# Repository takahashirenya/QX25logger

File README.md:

# QX25logger
25年度鳥人間コンテストのロガー基盤

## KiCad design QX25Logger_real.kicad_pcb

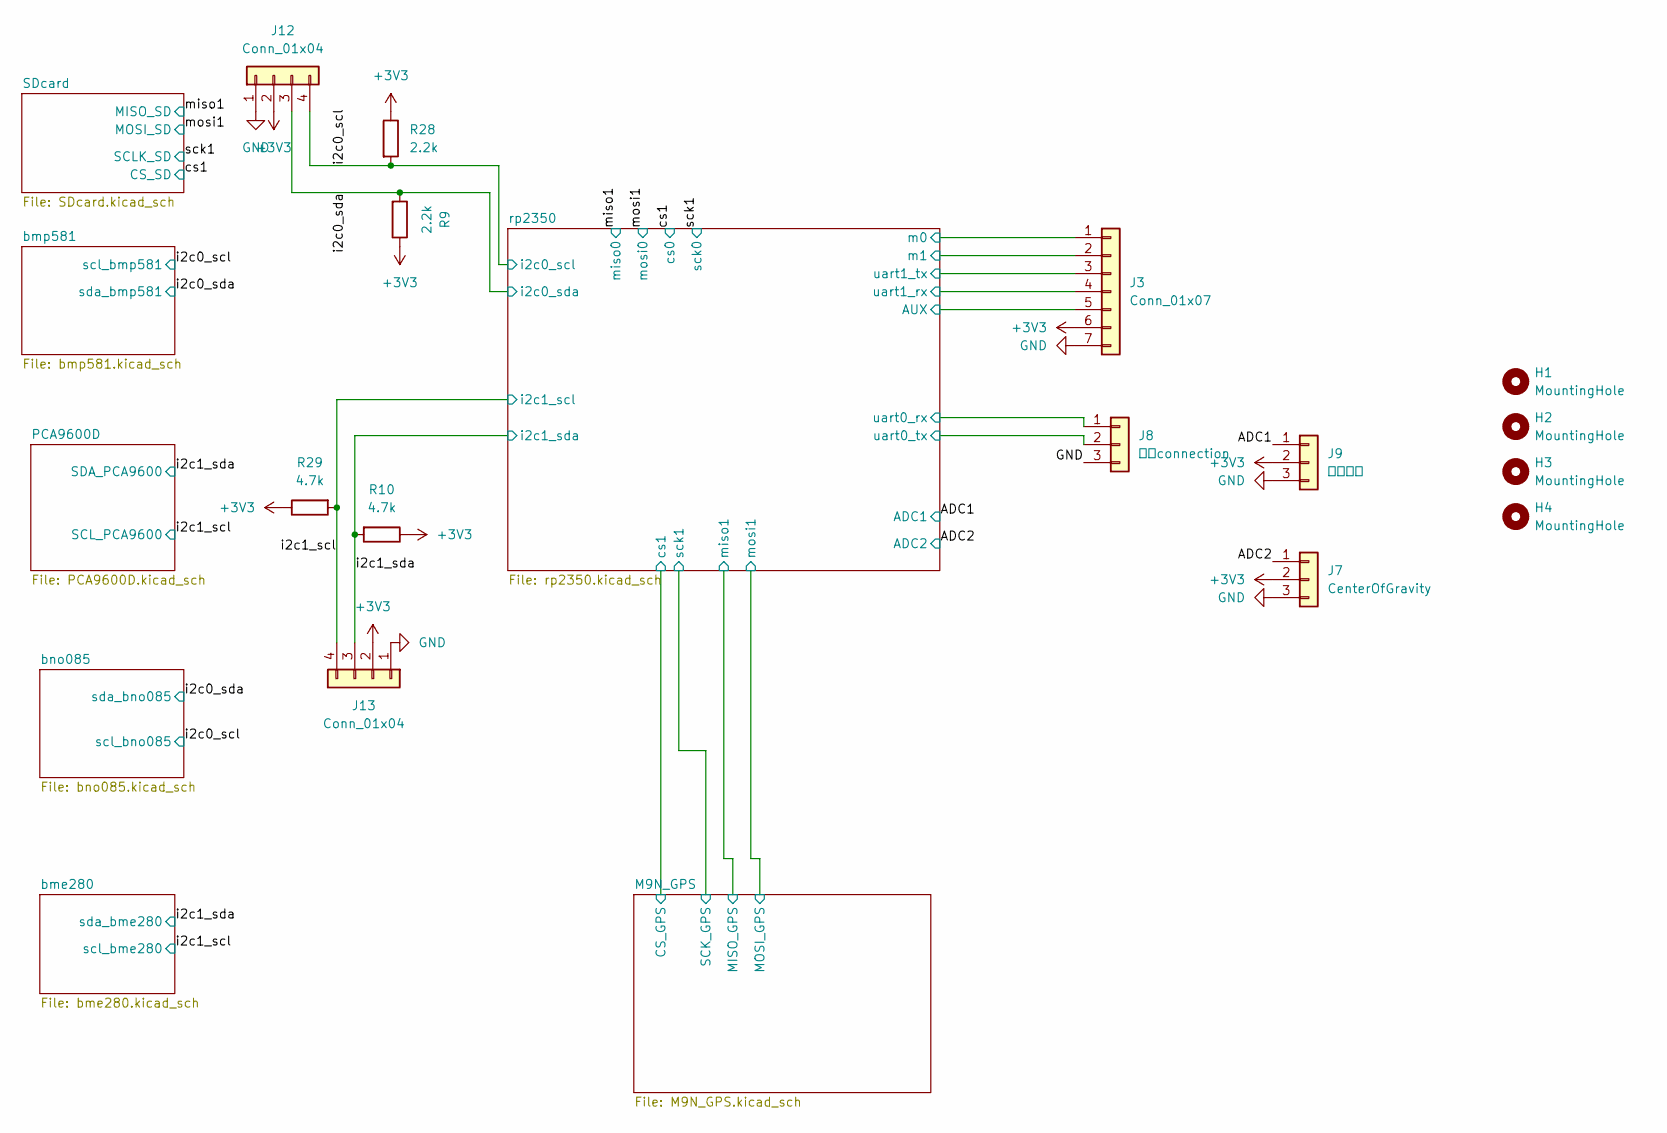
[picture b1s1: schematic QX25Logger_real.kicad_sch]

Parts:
H1, H2, H3, H4: MountingHole; MountingHole_3.2mm_M3
J3: Conn_01x07; PinHeader_1x07_P2.54mm_Vertical
J7: CenterOfGravity; JST_XH_B3B-XH-A_1x03_P2.50mm_Vertical
J8: 操舵connection; JST_XH_B3B-XH-AM_1x03_P2.50mm_Vertical
J9: 回転数計; JST_XH_B3B-XH-AM_1x03_P2.50mm_Vertical
J12, J13: Conn_01x04; JST_XH_B4B-XH-AM_1x04_P2.50mm_Vertical
R9, R28: 2.2k; R_0603_1608Metric
R10, R29: 4.7k; R_0603_1608Metric

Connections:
+3V3: J3.6, J7.2, J9.2, J12.2, J13.2, R9.1, R10.1, R28.1, R29.1; also elsewhere on the board
/ADC1: J9.1; also elsewhere on the board
/ADC2: J7.1; also elsewhere on the board
/i2c0_scl: J12.4, R28.2; also elsewhere on the board
/i2c0_sda: J12.3, R9.2; also elsewhere on the board
/i2c1_scl: J13.4, R29.2; also elsewhere on the board
/i2c1_sda: J13.3, R10.2; also elsewhere on the board
/rp2350/AUX: J3.5; also elsewhere on the board
/rp2350/m0: J3.1; also elsewhere on the board
/rp2350/m1: J3.2; also elsewhere on the board
/rp2350/uart0_rx: J8.1; also elsewhere on the board
/rp2350/uart0_tx: J8.2; also elsewhere on the board
/rp2350/uart1_rx: J3.4; also elsewhere on the board
/rp2350/uart1_tx: J3.3; also elsewhere on the board
GND: J3.7, J7.3, J8.3, J9.3, J12.1, J13.1; also elsewhere on the board

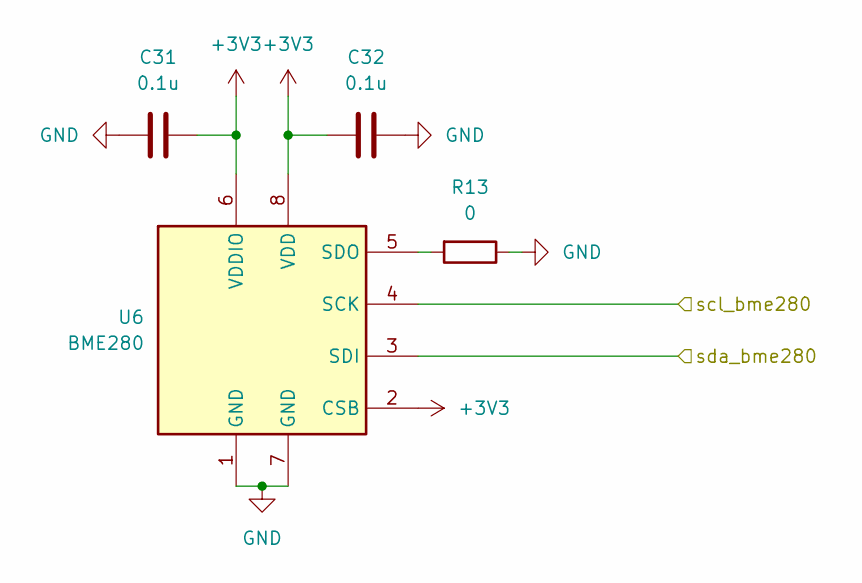
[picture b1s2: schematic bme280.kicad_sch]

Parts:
C31, C32: 0.1u; C_0805_2012Metric
R13: 0; R_0603_1608Metric
U6: BME280; Bosch_LGA-8_2.5x2.5mm_P0.65mm_ClockwisePinNumbering

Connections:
+3V3: C31.1, C32.1, U6.2 (CSB), U6.6 (VDDIO), U6.8 (VDD); also elsewhere on the board
/i2c1_scl: U6.4 (SCK); also elsewhere on the board
/i2c1_sda: U6.3 (SDI); also elsewhere on the board
GND: C31.2, C32.2, R13.1, U6.1 (GND), U6.7 (GND); also elsewhere on the board
unnamed: R13.2, U6.5 (SDO)

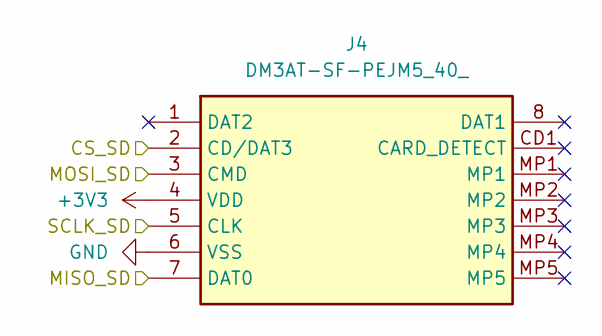
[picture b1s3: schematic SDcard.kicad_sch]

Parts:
J4: DM3AT-SF-PEJM5_40_; DM3ATSFPEJM540; Manufacturer_Part_Number DM3AT-SF-PEJM5(40); Mouser Part Number 798-DM3AT-SF-PEJM540

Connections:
+3V3: J4.4 (VDD); also elsewhere on the board
/cs1: J4.2 (CD/DAT3); also elsewhere on the board
/miso1: J4.7 (DAT0); also elsewhere on the board
/mosi1: J4.3 (CMD); also elsewhere on the board
/sck1: J4.5 (CLK); also elsewhere on the board
GND: J4.6 (VSS); also elsewhere on the board

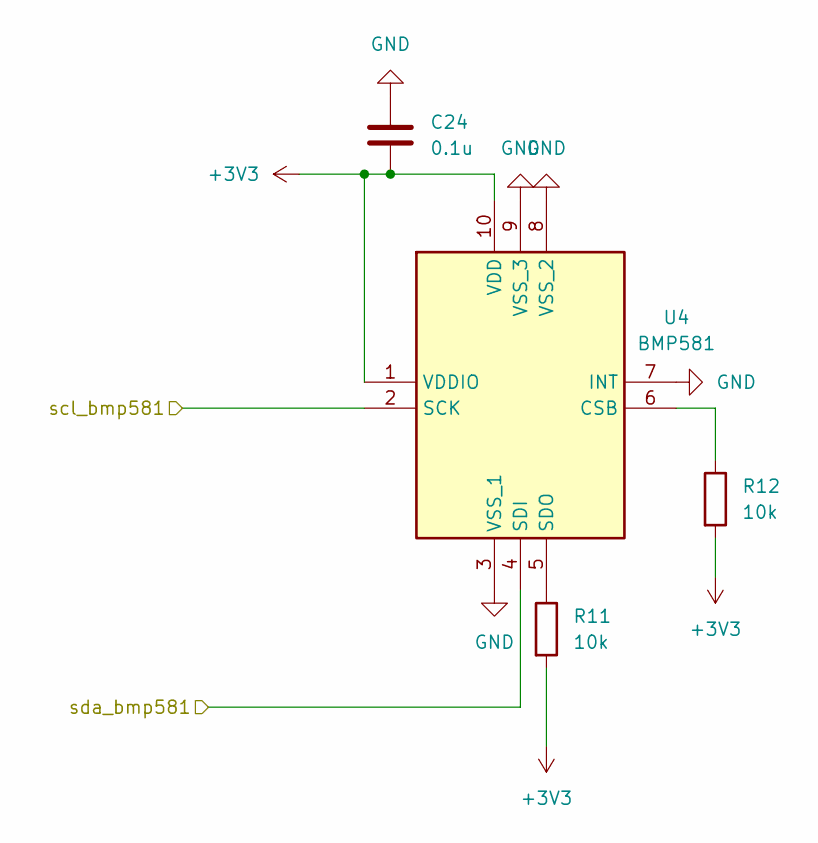
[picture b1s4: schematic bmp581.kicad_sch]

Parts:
C24: 0.1u; C_0805_2012Metric
R11, R12: 10k; R_0603_1608Metric
U4: BMP581; Manufacturer_Part_Number BMP581; Mouser Part Number 262-BMP581

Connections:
+3V3: C24.2, R11.2, R12.2, U4.1 (VDDIO), U4.10 (VDD); also elsewhere on the board
/i2c0_scl: U4.2 (SCK); also elsewhere on the board
/i2c0_sda: U4.4 (SDI); also elsewhere on the board
GND: C24.1, U4.3 (VSS_1), U4.7 (INT), U4.8 (VSS_2), U4.9 (VSS_3); also elsewhere on the board
unnamed: R12.1, U4.6 (CSB)
unnamed: R11.1, U4.5 (SDO)

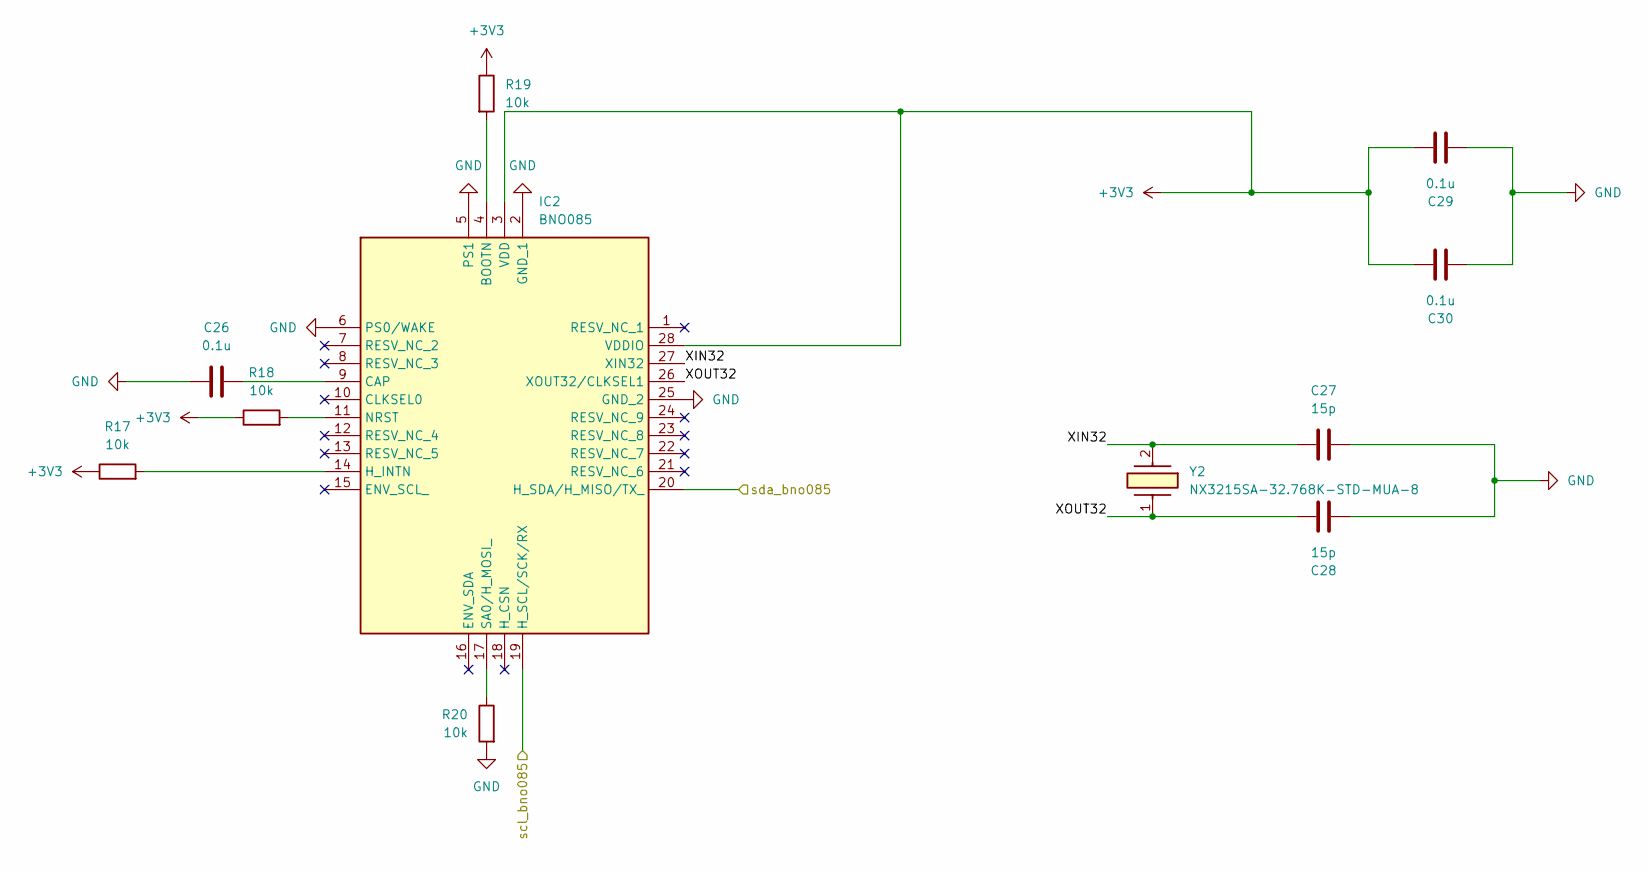
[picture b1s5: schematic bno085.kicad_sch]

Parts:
C26, C29, C30: 0.1u; C_0805_2012Metric
C27, C28: 15p; C_0805_2012Metric
IC2: BNO085; Manufacturer_Part_Number BNO085; Mouser Part Number 526-BNO085
R17, R19, R20: 10k; R_1206_3216Metric
R18: 10k; R_0603_1608Metric
Y2: NX3215SA-32.768K-STD-MUA-8; NX3215SA32768KSTDMUA8; Manufacturer_Part_Number NX3215SA-32.768K-STD-MUA-8; Mouser Part Number 344-NX3215SA32768K8

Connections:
+3V3: C29.1, C30.1, IC2.3 (VDD), IC2.28 (VDDIO), R17.1, R18.1, R19.1; also elsewhere on the board
/bno085/XIN32: C27.1, IC2.27 (XIN32), Y2.2 (CRYSTAL_2)
/bno085/XOUT32: C28.1, IC2.26 (XOUT32/CLKSEL1), Y2.1
/i2c0_scl: IC2.19 (H_SCL/SCK/RX); also elsewhere on the board
/i2c0_sda: IC2.20 (H_SDA/H_MISO/TX_); also elsewhere on the board
GND: C26.2, C27.2, C28.2, C29.2, C30.2, IC2.2 (GND_1), IC2.5 (PS1), IC2.6 (PS0/WAKE), IC2.25 (GND_2), R20.2; also elsewhere on the board
unnamed: IC2.4 (BOOTN), R19.2
unnamed: C26.1, IC2.9 (CAP)
unnamed: IC2.14 (H_INTN), R17.2
unnamed: IC2.11 (NRST), R18.2
unnamed: IC2.17 (SA0/H_MOSI_), R20.1

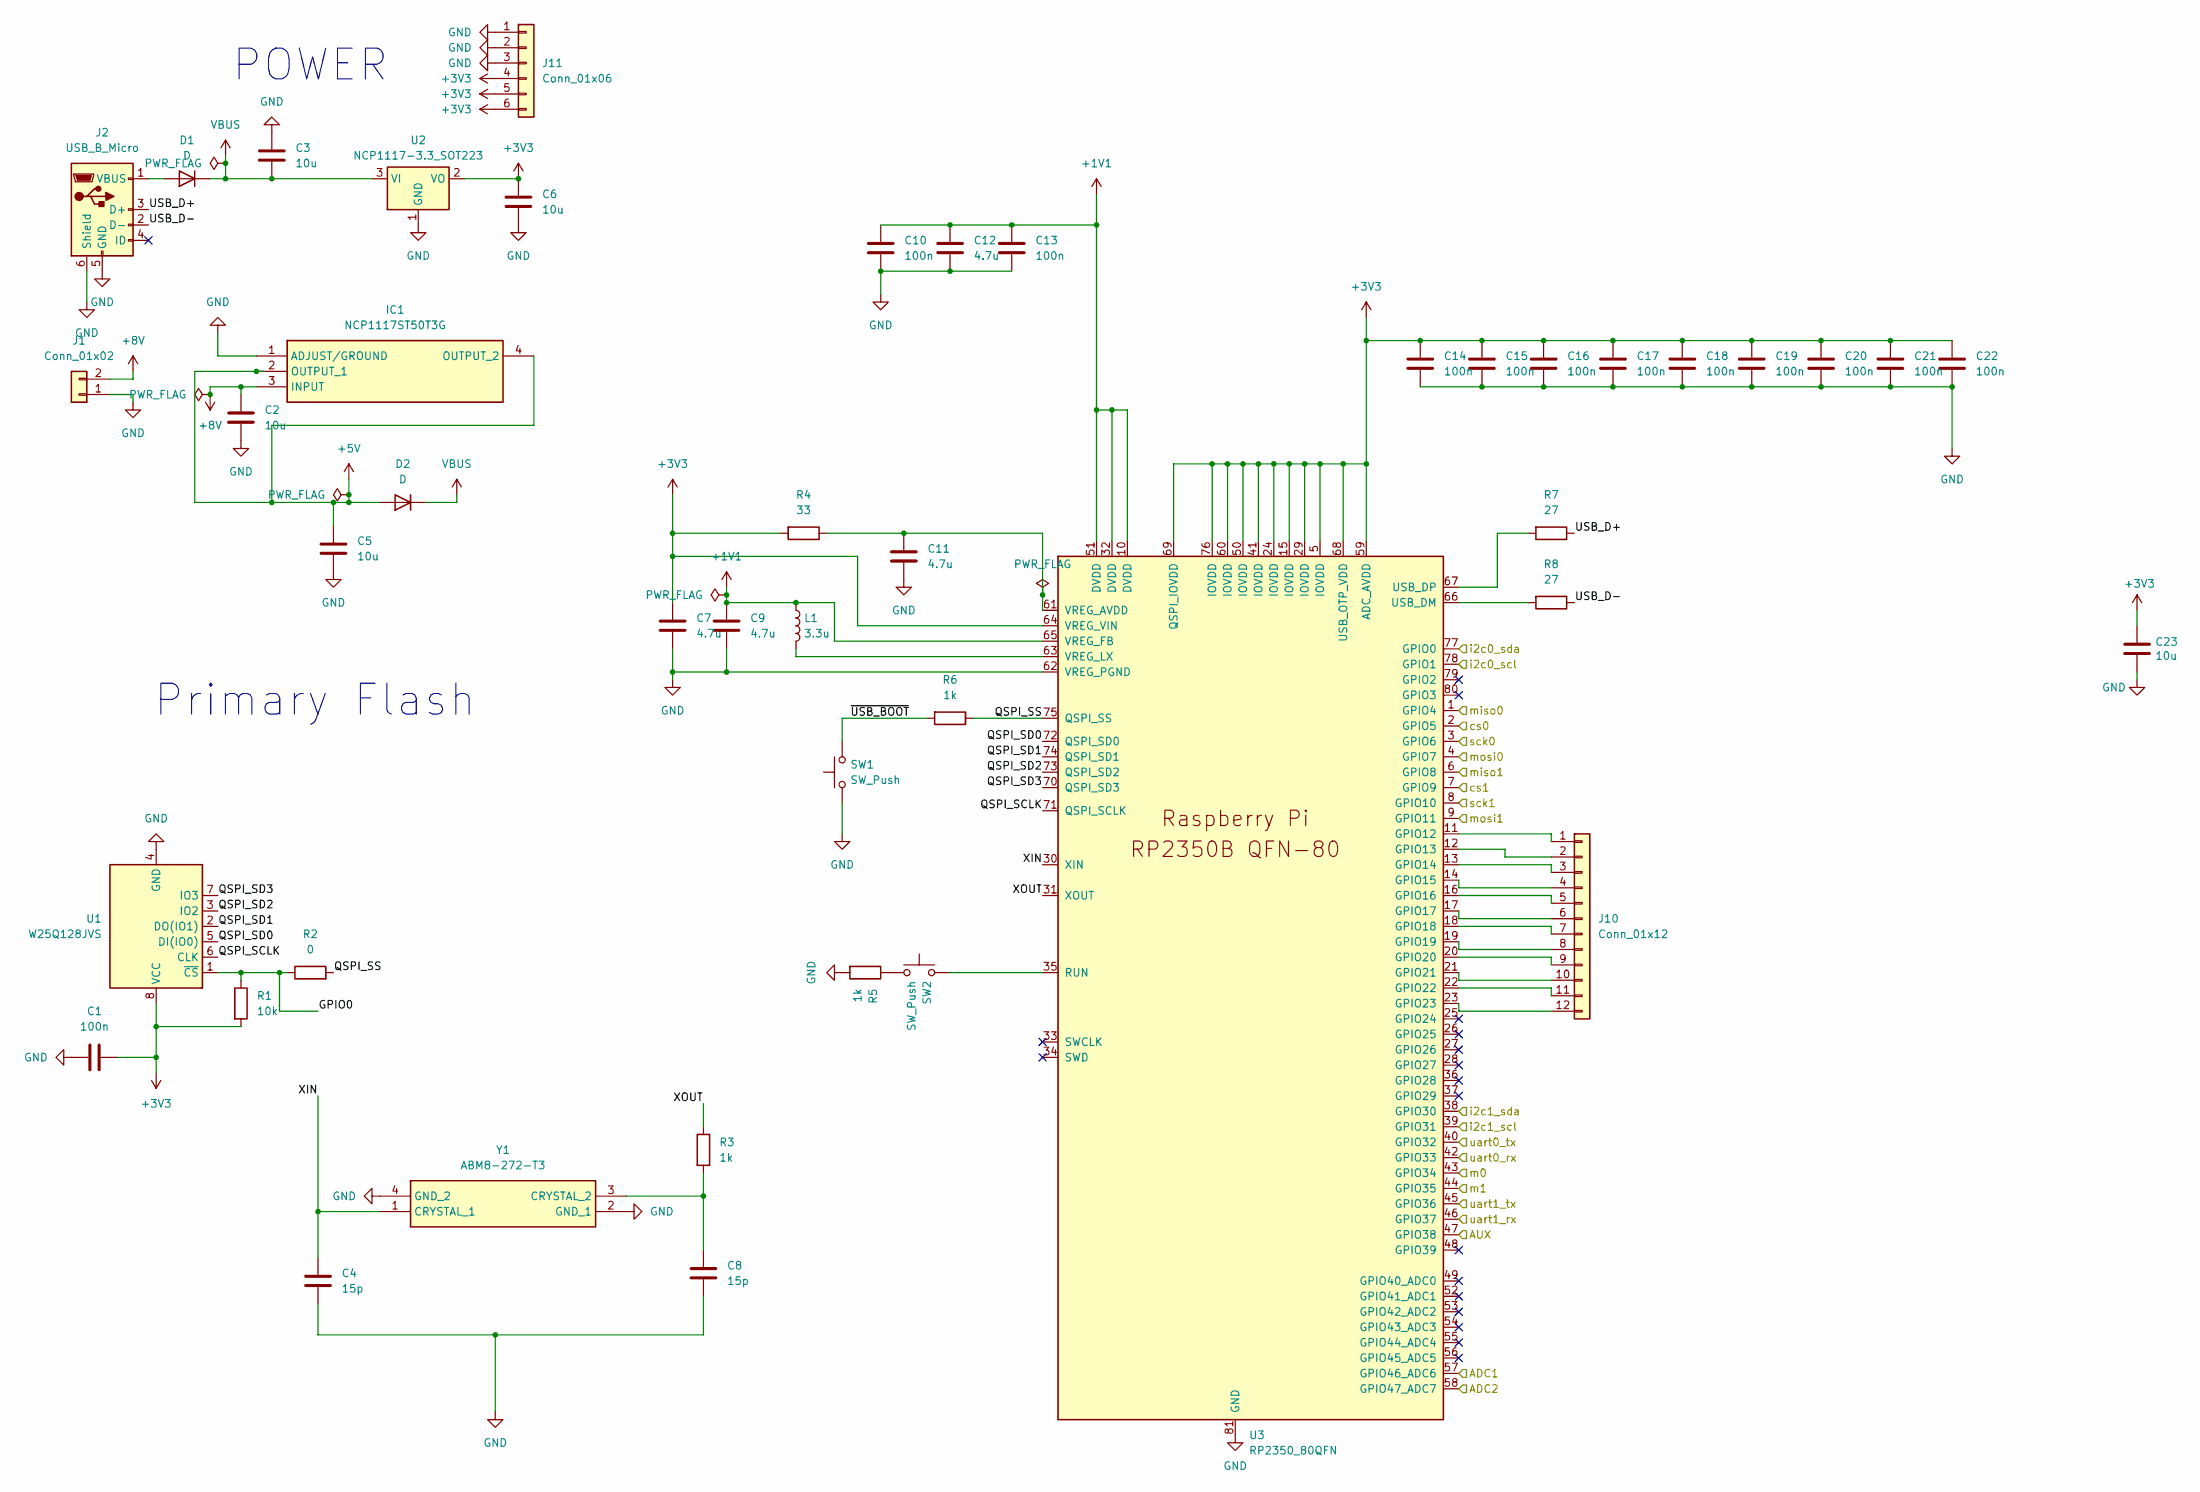
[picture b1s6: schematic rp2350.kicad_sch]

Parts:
C1, C10, C13, C14, C15, C16, C17, C18, C19, C20, C21, C22: 100n; C_0402_1005Metric
C2, C3, C5, C6, C23: 10u; C_0805_2012Metric
C4, C8: 15p; C_0402_1005Metric
C7, C9, C11, C12: 4.7u; C_0402_1005Metric
D1, D2: D; D_SMA
IC1: NCP1117ST50T3G; SOT230P700X180-4N; Manufacturer_Part_Number NCP1117ST50T3G; Mouser Part Number 863-NCP1117ST50T3G
J1: Conn_01x02; JST_VH_B2P-VH-B_1x02_P3.96mm_Vertical
J2: USB_B_Micro; 101181940001LF
J10: Conn_01x12; PinHeader_1x12_P2.54mm_Vertical
J11: Conn_01x06; PinHeader_1x06_P2.54mm_Vertical
L1: 3.3u; L_pol_2016
R1: 10k; C_0402_1005Metric
R2: 0; C_0402_1005Metric
R3, R5, R6: 1k; C_0402_1005Metric
R4: 33; C_0402_1005Metric
R7, R8: 27; C_0402_1005Metric
SW1, SW2: SW_Push; SW_Push_1P1T_NO_Vertical_Wuerth_434133025816
U1: W25Q128JVS; SOIC-8_5.23x5.23mm_P1.27mm
U2: NCP1117-3.3_SOT223; SOT-223-3_TabPin2
U3: RP2350_80QFN; RP2350-QFN-80-1EP_10x10_P0.4mm_EP3.4x3.4mm_ThermalVias
Y1: ABM8-272-T3; ABM8272T3; Manufacturer_Part_Number ABM8-272-T3; Mouser Part Number 815-ABM8-272-T3

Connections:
+1V1: C9.1, C10.1, C12.1, C13.1, L1.1, U3.10 (DVDD), U3.32 (DVDD), U3.51 (DVDD), U3.65 (VREG_FB)
+3V3: C1.2, C6.1, C7.1, C14.1, C15.1, C16.1, C17.1, C18.1, C19.1, C20.1, C21.1, C22.1, C23.1, J11.4, J11.5, J11.6, R1.2, R4.2, U1.8 (VCC), U2.2 (VO), U3.5 (IOVDD), U3.15 (IOVDD), U3.24 (IOVDD), U3.29 (IOVDD), U3.41 (IOVDD), U3.50 (IOVDD), U3.59 (ADC_AVDD), U3.60 (IOVDD), U3.64 (VREG_VIN), U3.68 (USB_OTP_VDD), U3.69 (QSPI_IOVDD), U3.76 (IOVDD); also elsewhere on the board
+5V: C5.1, D2.2 (A), IC1.2 (OUTPUT_1), IC1.4 (OUTPUT_2)
+8V: C2.1, IC1.3 (INPUT), J1.2
/ADC1: U3.57 (GPIO46_ADC6); also elsewhere on the board
/ADC2: U3.58 (GPIO47_ADC7); also elsewhere on the board
/M9N_GPS/CS_GPS: U3.7 (GPIO9); also elsewhere on the board
/M9N_GPS/MISO_GPS: U3.6 (GPIO8); also elsewhere on the board
/M9N_GPS/MOSI_GPS: U3.9 (GPIO11); also elsewhere on the board
/M9N_GPS/SCK_GPS: U3.8 (GPIO10); also elsewhere on the board
/cs1: U3.2 (GPIO5); also elsewhere on the board
/i2c0_scl: U3.78 (GPIO1); also elsewhere on the board
/i2c0_sda: U3.77 (GPIO0); also elsewhere on the board
/i2c1_scl: U3.39 (GPIO31); also elsewhere on the board
/i2c1_sda: U3.38 (GPIO30); also elsewhere on the board
/miso1: U3.1 (GPIO4); also elsewhere on the board
/mosi1: U3.4 (GPIO7); also elsewhere on the board
/rp2350/AUX: U3.47 (GPIO38); also elsewhere on the board
/rp2350/GPIO0: R1.1, R2.1, U1.1 (~CS)
/rp2350/QSPI_SCLK: U1.6 (CLK), U3.71 (QSPI_SCLK)
/rp2350/QSPI_SD0: U1.5 (DI(IO0)), U3.72 (QSPI_SD0)
/rp2350/QSPI_SD1: U1.2 (DO(IO1)), U3.74 (QSPI_SD1)
/rp2350/QSPI_SD2: U1.3 (IO2), U3.73 (QSPI_SD2)
/rp2350/QSPI_SD3: U1.7 (IO3), U3.70 (QSPI_SD3)
/rp2350/QSPI_SS: R2.2, R6.1, U3.75 (QSPI_SS)
/rp2350/USB_D+: J2.3 (D+), R7.1
/rp2350/USB_D-: J2.2 (D-), R8.1
/rp2350/XIN: C4.1, U3.30 (XIN), Y1.1 (CRYSTAL_1)
/rp2350/XOUT: R3.1, U3.31 (XOUT)
/rp2350/m0: U3.43 (GPIO34); also elsewhere on the board
/rp2350/m1: U3.44 (GPIO35); also elsewhere on the board
/rp2350/uart0_rx: U3.42 (GPIO33); also elsewhere on the board
/rp2350/uart0_tx: U3.40 (GPIO32); also elsewhere on the board
/rp2350/uart1_rx: U3.46 (GPIO37); also elsewhere on the board
/rp2350/uart1_tx: U3.45 (GPIO36); also elsewhere on the board
/rp2350/~USB_BOOT: R6.2, SW1.2
/sck1: U3.3 (GPIO6); also elsewhere on the board
GND: C1.1, C2.2, C3.1, C4.2, C5.2, C6.2, C7.2, C8.2, C9.2, C10.2, C11.2, C12.2, C13.2, C14.2, C15.2, C16.2, C17.2, C18.2, C19.2, C20.2, C21.2, C22.2, C23.2, IC1.1 (ADJUST/GROUND), J1.1, J2.5 (GND), J2.6 (Shield), J11.1, J11.2, J11.3, R5.2, SW1.1, U1.4 (GND), U2.1 (GND), U3.62 (VREG_PGND), U3.81 (GND), Y1.2 (GND_1), Y1.4 (GND_2); also elsewhere on the board
unnamed: D1.2 (A), J2.1 (VBUS)
unnamed: J10.1, U3.11 (GPIO12)
unnamed: J10.2, U3.12 (GPIO13)
unnamed: J10.3, U3.13 (GPIO14)
unnamed: J10.4, U3.14 (GPIO15)
unnamed: J10.5, U3.16 (GPIO16)
unnamed: J10.6, U3.17 (GPIO17)
unnamed: J10.7, U3.18 (GPIO18)
unnamed: J10.8, U3.19 (GPIO19)
unnamed: J10.9, U3.20 (GPIO20)
unnamed: J10.10, U3.21 (GPIO21)
unnamed: J10.11, U3.22 (GPIO22)
unnamed: J10.12, U3.23 (GPIO23)
unnamed: R5.1, SW2.1
unnamed: SW2.2, U3.35 (RUN)
unnamed: R8.2, U3.66 (USB_DM)
unnamed: R7.2, U3.67 (USB_DP)
unnamed: C11.1, R4.1, U3.61 (VREG_AVDD)
unnamed: L1.2, U3.63 (VREG_LX)
unnamed: C8.1, R3.2, Y1.3 (CRYSTAL_2)
VBUS: C3.2, D1.1 (K), D2.1 (K), U2.3 (VI)

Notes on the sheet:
POWER
Primary Flash

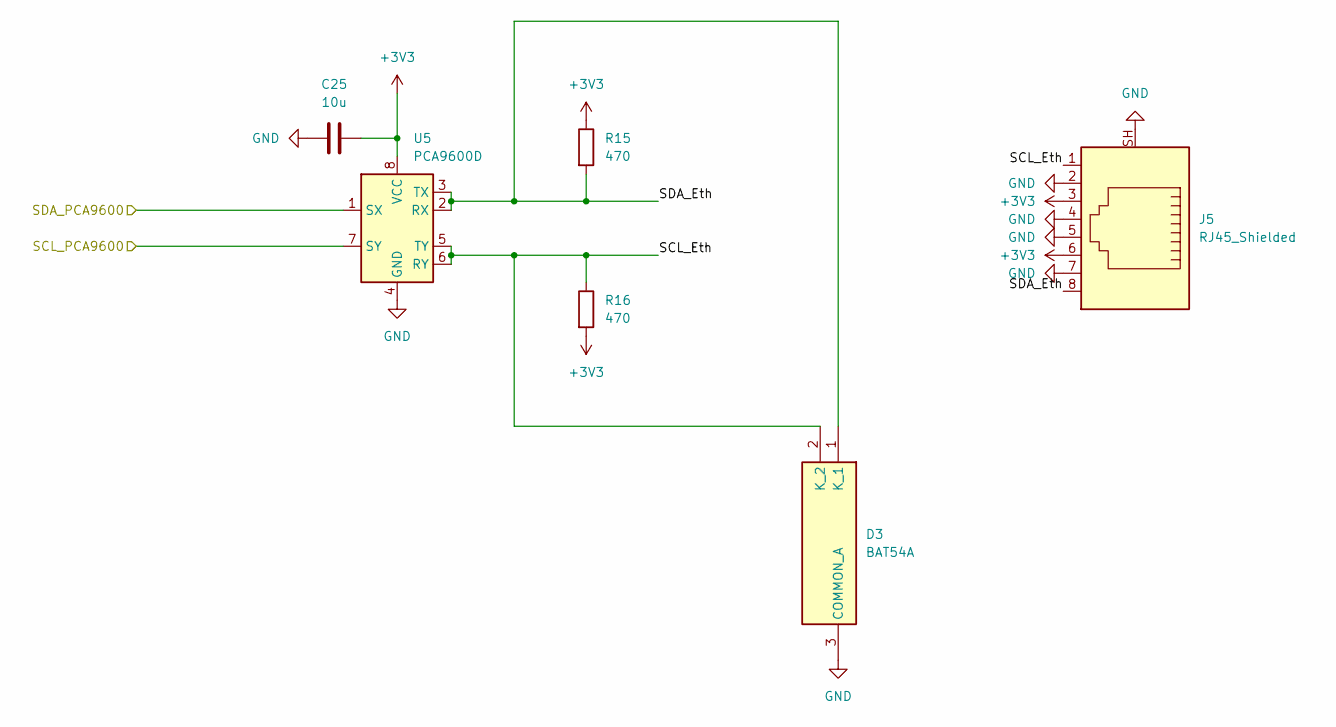
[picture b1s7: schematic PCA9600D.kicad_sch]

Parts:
C25: 10u; C_0805_2012Metric
D3: BAT54A; SOT95P240X110-3N; Manufacturer_Part_Number BAT54A; Mouser Part Number 583-BAT54A
J5: RJ45_Shielded; RJ45_Amphenol_RJHSE538X
R15, R16: 470; R_0603_1608Metric
U5: PCA9600D; SO-8_3.9x4.9mm_P1.27mm

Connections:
+3V3: C25.2, J5.3, J5.6, R15.1, R16.2, U5.8 (VCC); also elsewhere on the board
/PCA9600D/SCL_Eth: D3.2 (K_2), J5.1, R16.1, U5.5 (TY), U5.6 (RY)
/PCA9600D/SDA_Eth: D3.1 (K_1), J5.8, R15.2, U5.2 (RX), U5.3 (TX)
/i2c1_scl: U5.7 (SY); also elsewhere on the board
/i2c1_sda: U5.1 (SX); also elsewhere on the board
GND: C25.1, D3.3 (COMMON_A), J5.2, J5.4, J5.5, J5.7, J5.SH, U5.4 (GND); also elsewhere on the board

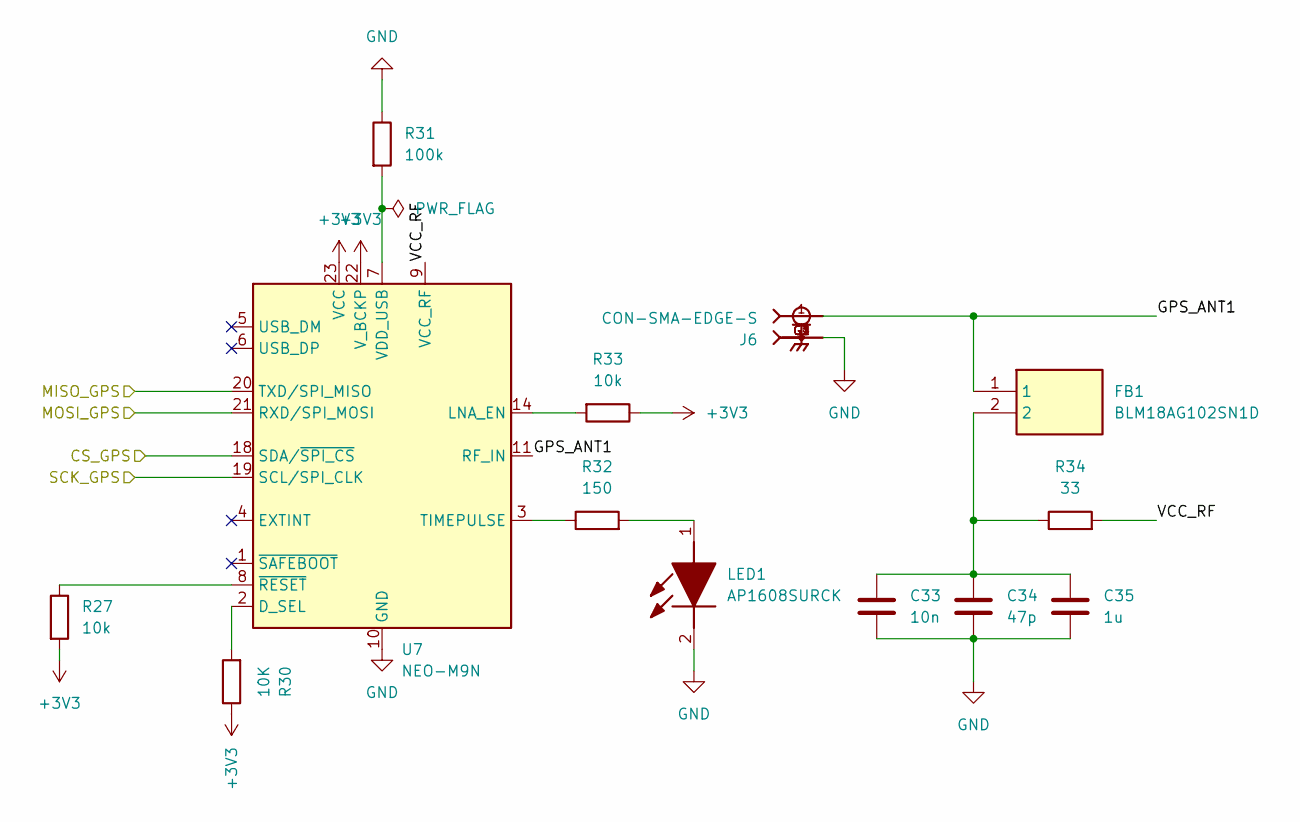
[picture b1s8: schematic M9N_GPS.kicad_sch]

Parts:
C33: 10n; C_0805_2012Metric
C34: 47p; C_0805_2012Metric
C35: 1u; C_0805_2012Metric
FB1: BLM18AG102SN1D; BLM18SP221SN1B; Manufacturer_Part_Number BLM18AG102SN1D; Mouser Part Number 81-BLM11A102S
J6: CON-SMA-EDGE-S; RFSOLUTIONS_CON-SMA-EDGE-S; PARTREV 1
LED1: AP1608SURCK; Manufacturer_Part_Number AP1608SURCK; Mouser Part Number 604-AP1608SURCK
R27, R33: 10k; R_0603_1608Metric
R30: 10K; R_0603_1608Metric
R31: 100k; R_0603_1608Metric
R32: 150; R_0603_1608Metric
R34: 33; R_0603_1608Metric
U7: NEO-M9N; ublox_NEO

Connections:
+3V3: R27.2, R30.1, R33.1, U7.22 (V_BCKP), U7.23 (VCC); also elsewhere on the board
/M9N_GPS/CS_GPS: U7.18 (SDA/~SPI_CS); also elsewhere on the board
/M9N_GPS/GPS_ANT1: FB1.1, J6.1, U7.11 (RF_IN)
/M9N_GPS/MISO_GPS: U7.20 (TXD/SPI_MISO); also elsewhere on the board
/M9N_GPS/MOSI_GPS: U7.21 (RXD/SPI_MOSI); also elsewhere on the board
/M9N_GPS/SCK_GPS: U7.19 (SCL/SPI_CLK); also elsewhere on the board
/M9N_GPS/VCC_RF: R34.2, U7.9 (VCC_RF)
GND: C33.2, C34.2, C35.2, J6.G1, J6.G2, J6.G3, J6.G4, LED1.2 (K), R31.1, U7.10 (GND), U7.12 (GND), U7.13 (GND), U7.24 (GND); also elsewhere on the board
unnamed: C33.1, C34.1, C35.1, FB1.2, R34.1
unnamed: LED1.1 (A), R32.2
unnamed: R30.2, U7.2 (D_SEL)
unnamed: R33.2, U7.14 (LNA_EN)
unnamed: R32.1, U7.3 (TIMEPULSE)
unnamed: R31.2, U7.7 (VDD_USB)
unnamed 77: R27.1, U7.8 (~RESET); also elsewhere on the board

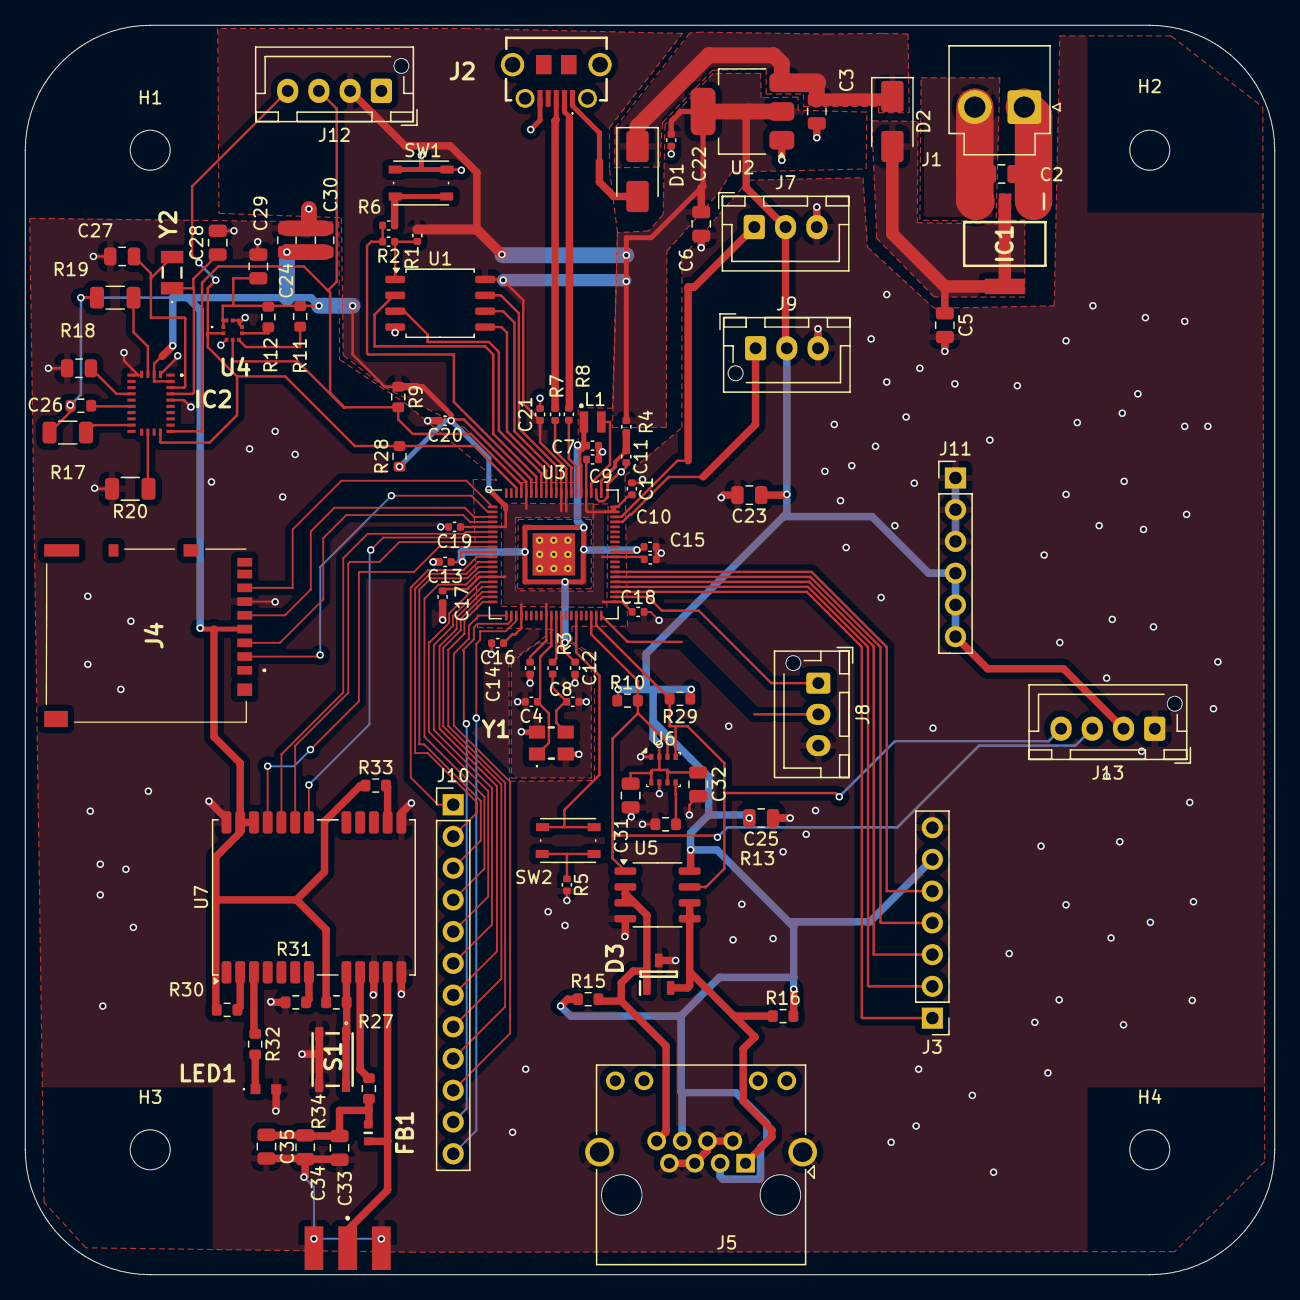
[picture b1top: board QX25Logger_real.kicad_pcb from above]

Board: 2 copper layers, 100.0 x 100.0 mm, 99 parts (0 on the bottom side), 80 nets.

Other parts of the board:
S1: SKRPACE010; SMT_4.2X3.2_

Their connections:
GND: S1.3, S1.4; also elsewhere on the board
unnamed 77: S1.1, S1.2; also elsewhere on the board

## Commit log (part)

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2025-12-04 2025/12/04
